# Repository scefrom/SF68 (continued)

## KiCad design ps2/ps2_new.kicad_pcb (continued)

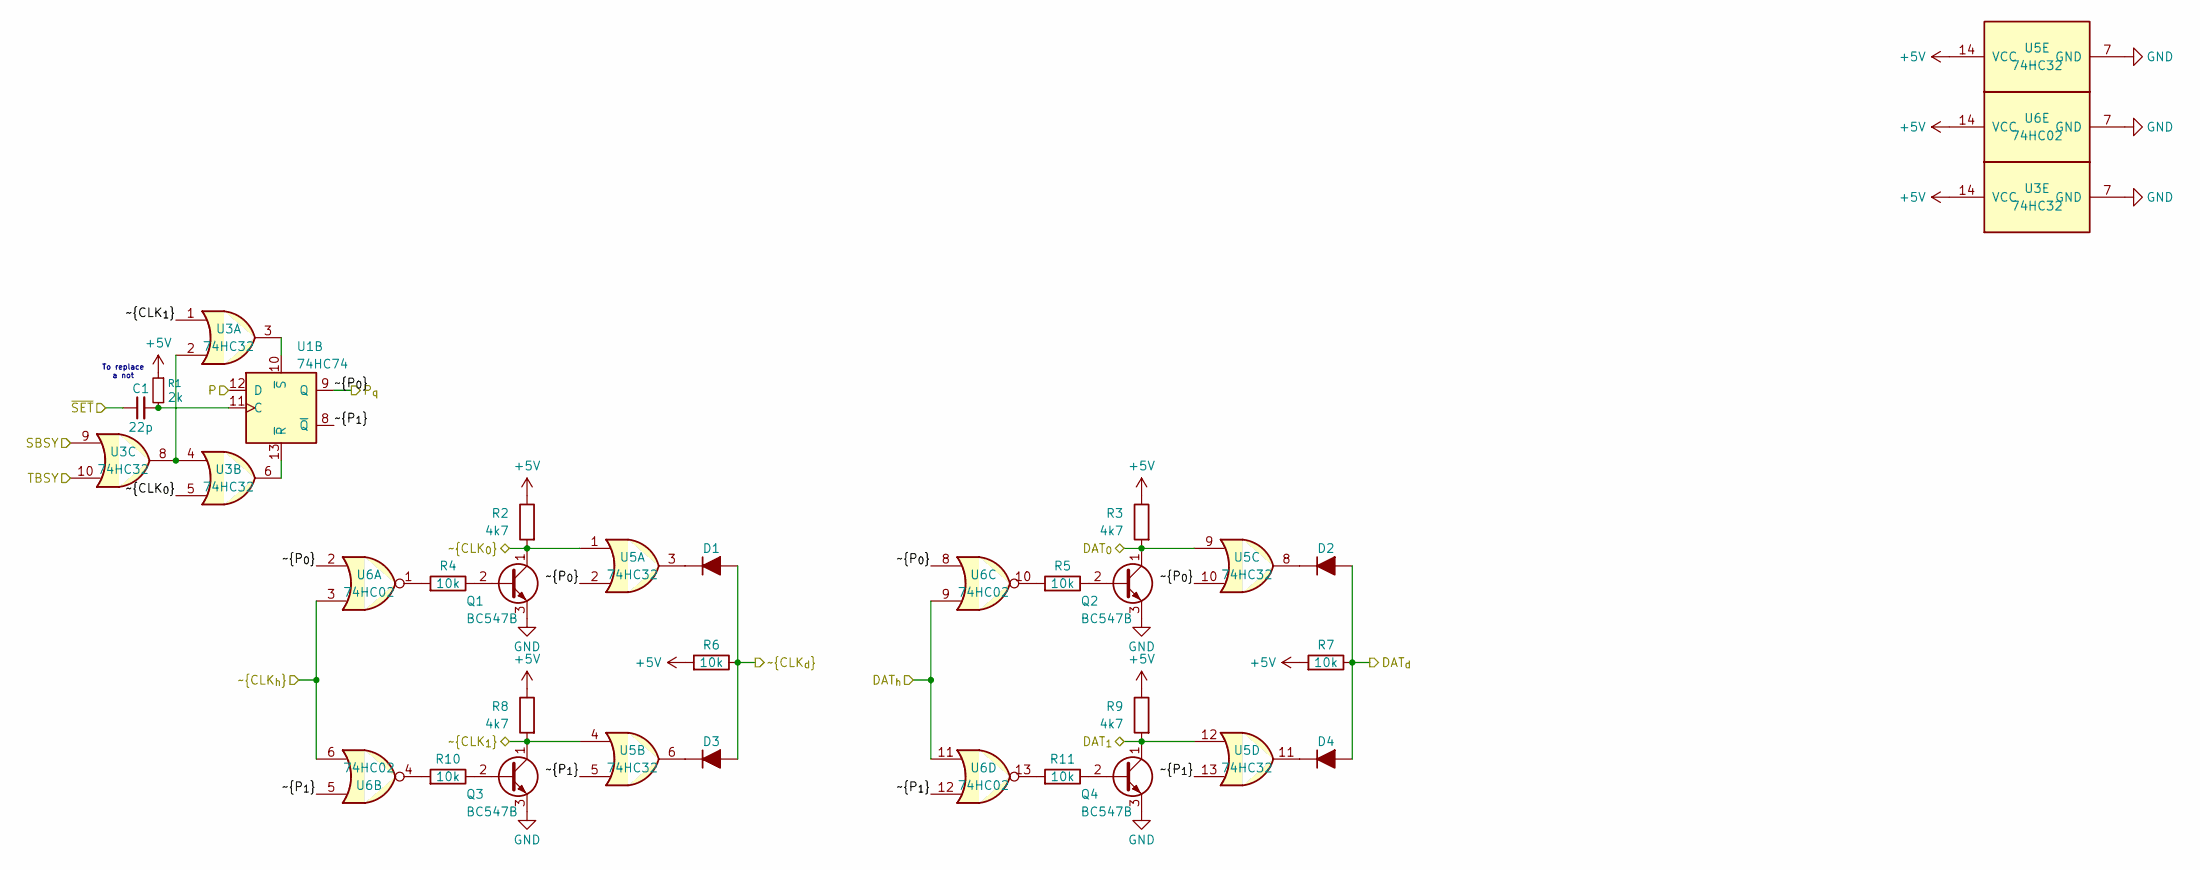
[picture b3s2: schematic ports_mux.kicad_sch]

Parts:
C1: 22p; C_Disc_D3.0mm_W1.6mm_P2.54mm
D1, D2, D3, D4: schotty; D_DO-35_SOD27_P2.54mm_Vertical_AnodeUp
Q1, Q2, Q3, Q4: BC547B; TO-92
R1: 2k; R_Axial_DIN0207_L6.3mm_D2.5mm_P2.54mm_Vertical
R2, R3, R8, R9: 4k7; R_Axial_DIN0207_L6.3mm_D2.5mm_P2.54mm_Vertical
R4, R5, R6, R7, R10, R11: 10k; R_Axial_DIN0207_L6.3mm_D2.5mm_P2.54mm_Vertical
U1: 74HC74; DIP-14_W7.62mm
U3, U5: 74HC32; DIP-14_W7.62mm
U6: 74HC02; DIP-14_W7.62mm

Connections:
+5V: R1.1, R2.1, R3.1, R6.2, R7.2, R8.1, R9.1, U3.14 (VCC), U5.14 (VCC), U6.14 (VCC); also elsewhere on the board
/A_{1}: U1.12 (D); also elsewhere on the board
/DAT_{0}: Q2.1 (C), R3.2, U5.9; also elsewhere on the board
/DAT_{1}: Q4.1 (C), R9.2, U5.12; also elsewhere on the board
/DAT_{d}: D2.2 (A), D4.2 (A), R7.1; also elsewhere on the board
/DAT_{h}: U6.9, U6.11; also elsewhere on the board
/PORT: U1.9 (Q), U5.2, U5.10, U6.2, U6.8; also elsewhere on the board
/SBSY: U3.9; also elsewhere on the board
/TBSY: U3.10; also elsewhere on the board
/ports_mux/~P_{1}: U1.8 (~Q), U5.5, U5.13, U6.5, U6.12
/~CLK_{0}: Q1.1 (C), R2.2, U3.5, U5.1; also elsewhere on the board
/~CLK_{1}: Q3.1 (C), R8.2, U3.1, U5.4; also elsewhere on the board
/~CLK_{d}: D1.2 (A), D3.2 (A), R6.1; also elsewhere on the board
/~CLK_{h}: U6.3, U6.6; also elsewhere on the board
/~W: C1.1; also elsewhere on the board
GND: Q1.3 (E), Q2.3 (E), Q3.3 (E), Q4.3 (E), U3.7 (GND), U5.7 (GND), U6.7 (GND); also elsewhere on the board
unnamed: D1.1 (K), U5.3
unnamed: D2.1 (K), U5.8
unnamed: D3.1 (K), U5.6
unnamed: D4.1 (K), U5.11
unnamed: Q1.2 (B), R4.1
unnamed: Q2.2 (B), R5.1
unnamed: Q3.2 (B), R10.1
unnamed: Q4.2 (B), R11.1
unnamed: R4.2, U6.1
unnamed: R5.2, U6.10
unnamed: R10.2, U6.4
unnamed: R11.2, U6.13
unnamed: C1.2, R1.2, U1.11 (C)
unnamed: U1.13 (~R), U3.6
unnamed: U1.10 (~S), U3.3
unnamed: U3.2, U3.4, U3.8

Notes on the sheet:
To replace a not

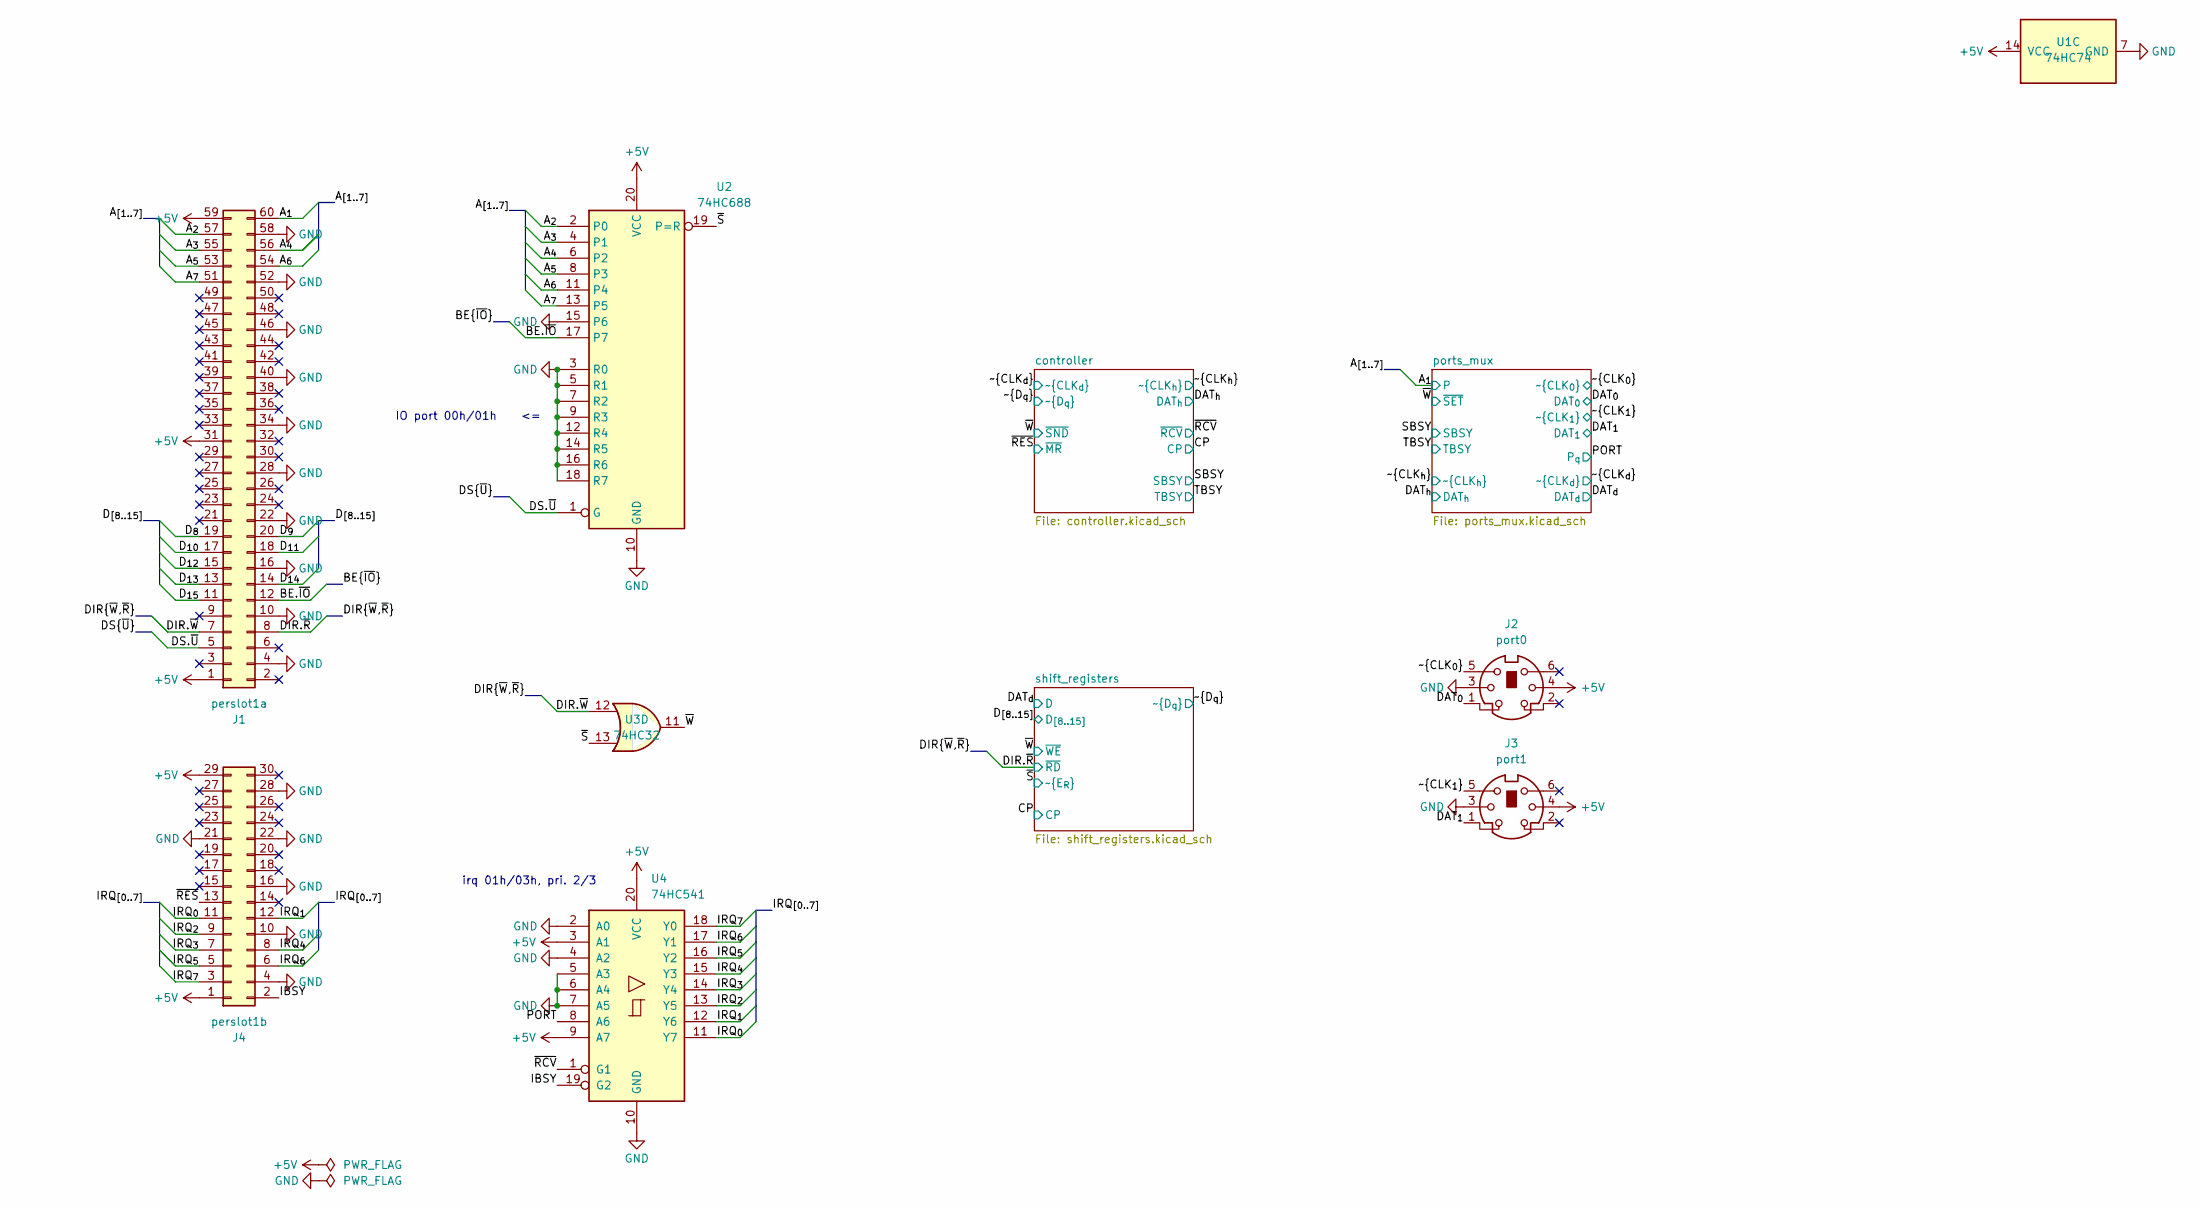
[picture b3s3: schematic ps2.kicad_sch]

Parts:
J1: perslot1a; pcb_edge_60_P2.54_new
J2: port0; 57492651
J3: port1; 57492651
J4: perslot1b; pcb_edge_30_P2.54_new
U1: 74HC74; DIP-14_W7.62mm
U2: 74HC688; DIP-20_W7.62mm
U3: 74HC32; DIP-14_W7.62mm
U4: 74HC541; DIP-20_W7.62mm

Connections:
+5V: J1.1, J1.31, J1.59, J2.4, J3.4, J4.1, J4.29, U1.14 (VCC), U2.20 (VCC), U4.3 (A1), U4.9 (A7), U4.20 (VCC); also elsewhere on the board
/A_{1}: J1.60; also elsewhere on the board
/A_{2}: J1.57, U2.2 (P0)
/A_{3}: J1.55, U2.4 (P1)
/A_{4}: J1.56, U2.6 (P2)
/A_{5}: J1.53, U2.8 (P3)
/A_{6}: J1.54, U2.11 (P4)
/A_{7}: J1.51, U2.13 (P5)
/BE.~IO: J1.12, U2.17 (P7)
/DAT_{0}: J2.1; also elsewhere on the board
/DAT_{1}: J3.1; also elsewhere on the board
/DIR.~R: J1.8; also elsewhere on the board
/DIR.~W: J1.7, U3.12
/DS.~U: J1.5, U2.1 (G)
/D_{8}: J1.19; also elsewhere on the board
/D_{9}: J1.20; also elsewhere on the board
/D_{10}: J1.17; also elsewhere on the board
/D_{11}: J1.18; also elsewhere on the board
/D_{12}: J1.15; also elsewhere on the board
/D_{13}: J1.13; also elsewhere on the board
/D_{14}: J1.14; also elsewhere on the board
/D_{15}: J1.11; also elsewhere on the board
/IBSY: J4.2, U4.19 (G2)
/IRQ_{0}: J4.11, U4.11 (Y7)
/IRQ_{1}: J4.12, U4.12 (Y6)
/IRQ_{2}: J4.9, U4.13 (Y5)
/IRQ_{3}: J4.7, U4.14 (Y4)
/IRQ_{4}: J4.8, U4.15 (Y3)
/IRQ_{5}: J4.5, U4.16 (Y2)
/IRQ_{6}: J4.6, U4.17 (Y1)
/IRQ_{7}: J4.3, U4.18 (Y0)
/PORT: U4.8 (A6); also elsewhere on the board
/~CLK_{0}: J2.5; also elsewhere on the board
/~CLK_{1}: J3.5; also elsewhere on the board
/~RCV: U4.1 (G1); also elsewhere on the board
/~RES: J4.13; also elsewhere on the board
/~S: U2.19 (P=R), U3.13; also elsewhere on the board
/~W: U3.11; also elsewhere on the board
GND: J1.4, J1.10, J1.16, J1.22, J1.28, J1.34, J1.40, J1.46, J1.52, J1.58, J2.3, J3.3, J4.4, J4.10, J4.16, J4.21, J4.22, J4.28, U1.7 (GND), U2.3 (R0), U2.5 (R1), U2.7 (R2), U2.9 (R3), U2.10 (GND), U2.12 (R4), U2.14 (R5), U2.15 (P6), U2.16 (R6), U2.18 (R7), U4.2 (A0), U4.4 (A2), U4.5 (A3), U4.6 (A4), U4.7 (A5), U4.10 (GND); also elsewhere on the board

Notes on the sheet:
IO port 00h/01h <=
irq 01h/03h, pri. 2/3

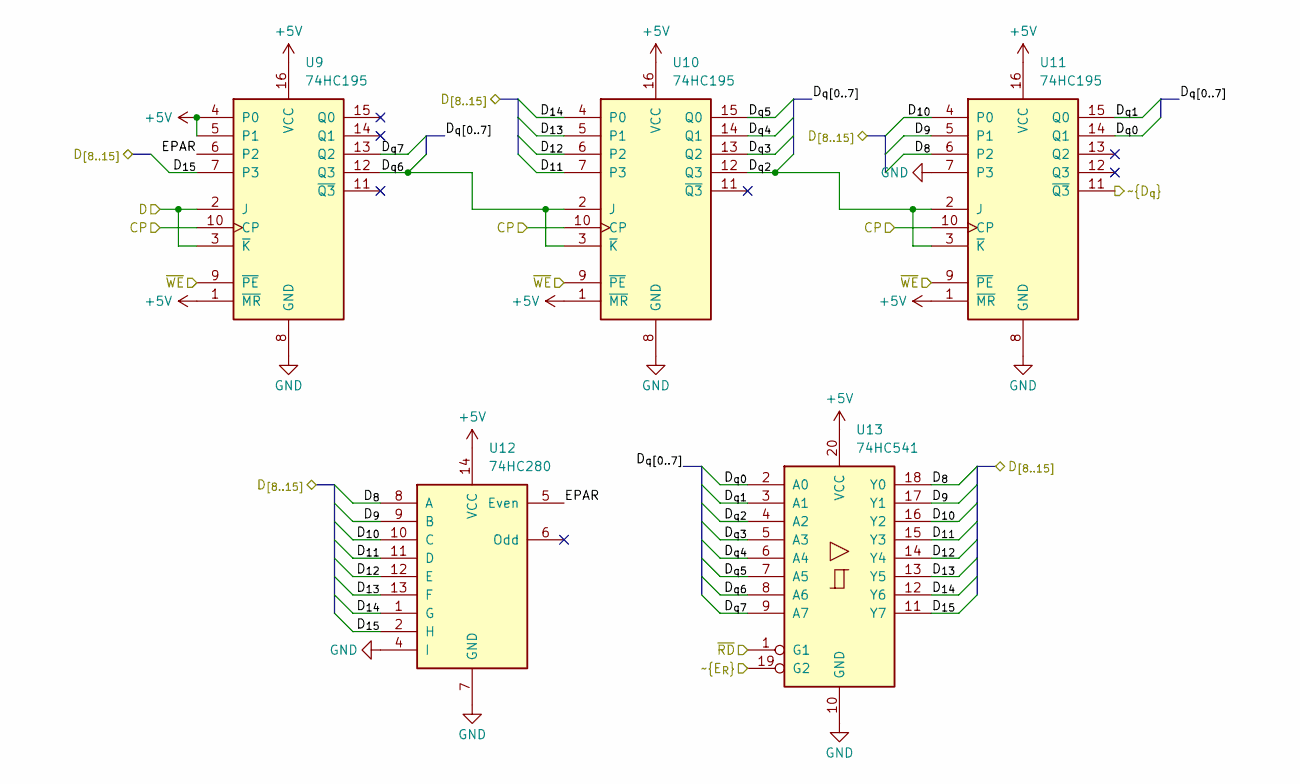
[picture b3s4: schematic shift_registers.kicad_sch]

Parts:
U9, U10, U11: 74HC195; DIP-16_W7.62mm
U12: 74HC280; DIP-14_W7.62mm
U13: 74HC541; DIP-20_W7.62mm

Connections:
+5V: U9.1 (~MR), U9.4 (P0), U9.5 (P1), U9.16 (VCC), U10.1 (~MR), U10.16 (VCC), U11.1 (~MR), U11.16 (VCC), U12.14 (VCC), U13.20 (VCC); also elsewhere on the board
/CP: U9.10 (CP), U10.10 (CP), U11.10 (CP); also elsewhere on the board
/DAT_{d}: U9.2 (J), U9.3 (~K); also elsewhere on the board
/DIR.~R: U13.1 (G1); also elsewhere on the board
/D_{8}: U11.6 (P2), U12.8 (A), U13.18 (Y0); also elsewhere on the board
/D_{9}: U11.5 (P1), U12.9 (B), U13.17 (Y1); also elsewhere on the board
/D_{10}: U11.4 (P0), U12.10 (C), U13.16 (Y2); also elsewhere on the board
/D_{11}: U10.7 (P3), U12.11 (D), U13.15 (Y3); also elsewhere on the board
/D_{12}: U10.6 (P2), U12.12 (E), U13.14 (Y4); also elsewhere on the board
/D_{13}: U10.5 (P1), U12.13 (F), U13.13 (Y5); also elsewhere on the board
/D_{14}: U10.4 (P0), U12.1 (G), U13.12 (Y6); also elsewhere on the board
/D_{15}: U9.7 (P3), U12.2 (H), U13.11 (Y7); also elsewhere on the board
/shift_registers/D_{q0}: U11.14 (Q1), U13.2 (A0)
/shift_registers/D_{q1}: U11.15 (Q0), U13.3 (A1)
/shift_registers/D_{q2}: U10.12 (Q3), U11.2 (J), U11.3 (~K), U13.4 (A2)
/shift_registers/D_{q3}: U10.13 (Q2), U13.5 (A3)
/shift_registers/D_{q4}: U10.14 (Q1), U13.6 (A4)
/shift_registers/D_{q5}: U10.15 (Q0), U13.7 (A5)
/shift_registers/D_{q6}: U9.12 (Q3), U10.2 (J), U10.3 (~K), U13.8 (A6)
/shift_registers/D_{q7}: U9.13 (Q2), U13.9 (A7)
/shift_registers/EPAR: U9.6 (P2), U12.5 (Even)
/~D_{q}: U11.11 (~Q3); also elsewhere on the board
/~S: U13.19 (G2); also elsewhere on the board
/~W: U9.9 (~PE), U10.9 (~PE), U11.9 (~PE); also elsewhere on the board
GND: U9.8 (GND), U10.8 (GND), U11.7 (P3), U11.8 (GND), U12.4 (I), U12.7 (GND), U13.10 (GND); also elsewhere on the board

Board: 2 copper layers, 48 parts (0 on the bottom side), 85 nets, no tracks yet.

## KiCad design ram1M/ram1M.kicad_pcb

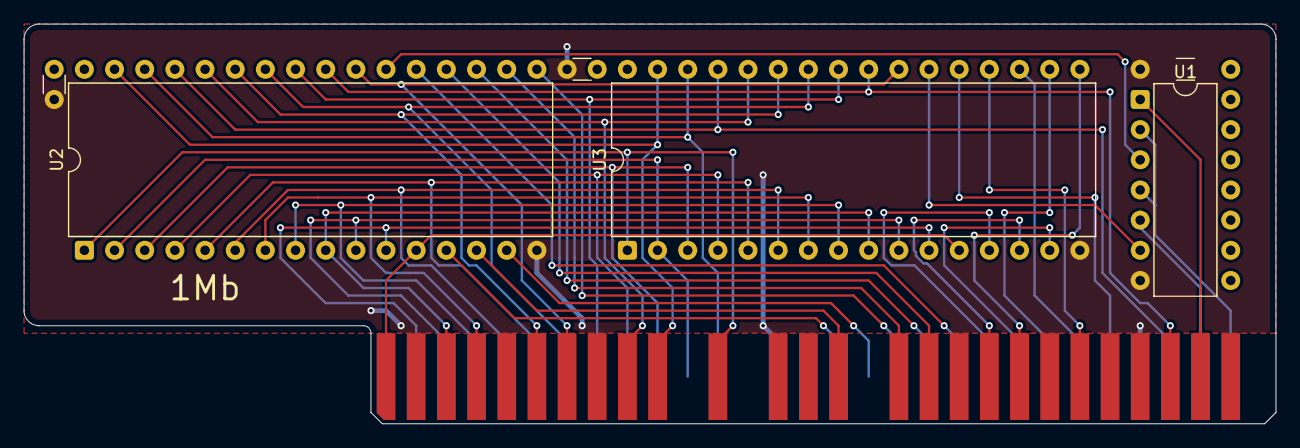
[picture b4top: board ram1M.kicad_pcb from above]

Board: 2 copper layers, 105.4 x 33.7 mm, 7 parts (0 on the bottom side), 44 nets.

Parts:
CB1, CB1#3: C_Disc_D3.0mm_W1.6mm_P2.54mm
CB1#2: C_Disc_D3.0mm_W1.6mm_P7.62mm
J5: ramslot; pcb_edge_60_P2.54_new
U1: 74HC32; DIP-14_W7.62mm
U2, U3: AS6C4008-55PCN; DIP-32_W15.24mm

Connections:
+5V: CB1.1, CB1#2.1, CB1#3.1, J5.2, J5.30, J5.60, U1.9, U1.10, U1.12, U1.13, U1.14 (VCC), U2.32 (VCC), U3.32 (VCC)
/A_{1}: J5.1, U2.12 (A0), U3.12 (A0)
/A_{2}: J5.4, U2.11 (A1), U3.11 (A1)
/A_{3}: J5.6, U2.10 (A2), U3.10 (A2)
/A_{4}: J5.5, U2.9 (A3), U3.9 (A3)
/A_{5}: J5.8, U2.8 (A4), U3.8 (A4)
/A_{6}: J5.7, U2.7 (A5), U3.7 (A5)
/A_{7}: J5.10, U2.6 (A6), U3.6 (A6)
/A_{8}: J5.12, U2.5 (A7), U3.5 (A7)
/A_{9}: J5.11, U2.27 (A8), U3.27 (A8)
/A_{10}: J5.14, U2.26 (A9), U3.26 (A9)
/A_{11}: J5.13, U2.23 (A10), U3.23 (A10)
/A_{12}: J5.16, U2.25 (A11), U3.25 (A11)
/A_{13}: J5.18, U2.4 (A12), U3.4 (A12)
/A_{14}: J5.17, U2.28 (A13), U3.28 (A13)
/A_{15}: J5.20, U2.3 (A14), U3.3 (A14)
/A_{16}: J5.19, U2.31 (A15), U3.31 (A15)
/A_{17}: J5.22, U2.2 (A16), U3.2 (A16)
/A_{18}: J5.24, U2.30 (A17), U3.30 (A17)
/A_{19}: J5.23, U2.1 (A18), U3.1 (A18)
/DIR.~R: J5.53, U2.24 (OE#), U3.24 (OE#)
/DIR.~W: J5.54, U2.29 (WE#), U3.29 (WE#)
/DS.~L: J5.55, U1.1
/DS.~U: J5.56, U1.5
/D_{0}: J5.32, U2.13 (DQ0)
/D_{1}: J5.31, U2.14 (DQ1)
/D_{2}: J5.34, U2.15 (DQ2)
/D_{3}: J5.36, U2.17 (DQ3)
/D_{4}: J5.35, U2.18 (DQ4)
/D_{5}: J5.38, U2.19 (DQ5)
/D_{6}: J5.37, U2.20 (DQ6)
/D_{7}: J5.40, U2.21 (DQ7)
/D_{8}: J5.42, U3.13 (DQ0)
/D_{9}: J5.41, U3.14 (DQ1)
/D_{10}: J5.44, U3.15 (DQ2)
/D_{11}: J5.43, U3.17 (DQ3)
/D_{12}: J5.46, U3.18 (DQ4)
/D_{13}: J5.48, U3.19 (DQ5)
/D_{14}: J5.47, U3.20 (DQ6)
/D_{15}: J5.50, U3.21 (DQ7)
/~BKE: J5.58, U1.2, U1.4
/~LS: U1.3, U2.22 (CE#)
/~US: U1.6, U3.22 (CE#)
GND: CB1.2, CB1#2.2, CB1#3.2, J5.3, J5.9, J5.15, J5.27, J5.28, J5.29, J5.39, J5.45, J5.49, J5.51, J5.52, J5.57, U1.7 (GND), U2.16 (VSS), U3.16 (VSS)
